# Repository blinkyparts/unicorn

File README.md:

# Rainbow Unicorn

This unicorn will bright up your life. The hair is glowing in all colours of the rainbow due to RGB-LEDs on the back. The soldering kit is very simple and easy to assamble.

The RGB-Effect looks like this, but much better in real :)

- Status: **Complete**
- Difficulty: **2/5**

### Parts List

| Description                   | Quantity |
|-------------------------------|----------|
| RGB LEDs 5mm                  |     4    |
| Button (SMD)                  |     1    |
| CR2032 Battery Holder (SMD)   |     1    |
| CR2032 Battery (not included) |     1    |

### Manual
You can find the manual and pictures of every step here: https://github.com/Binary-Kitchen/SolderingTutorial

### Copyright and Authorship

- Board: [CC-BY-SA 4.0](https://creativecommons.org/licenses/by-sa/4.0/) - Binary Kitchen e.V. and blinkyparts.com
- Unicorn SVG [CC-BY-SA](https://creativecommons.org/licenses/by-sa/4.0/) - [Unicorn by Mooms from the Noun Project](https://thenounproject.com/term/unicorn/2061795/) (We've bought a licence, you should honor the artist work too!)
- Idea and scheme: [CC-BY-SA 4.0](https://creativecommons.org/licenses/by-sa/4.0/) - [Timo Schindler @ blinkyparts.com](https://blinkyparts.com)

### Buy Soldering Kits
If you want to buy the parts and PCB for a soldering kit you can find everything here: [shop.blinkyparts.com](https://shop.blinkyparts.com/de/Regenbogen-Einhorn-Einfacher-Bausatz-fuer-einen-tollen-Anstecker/blink232242)

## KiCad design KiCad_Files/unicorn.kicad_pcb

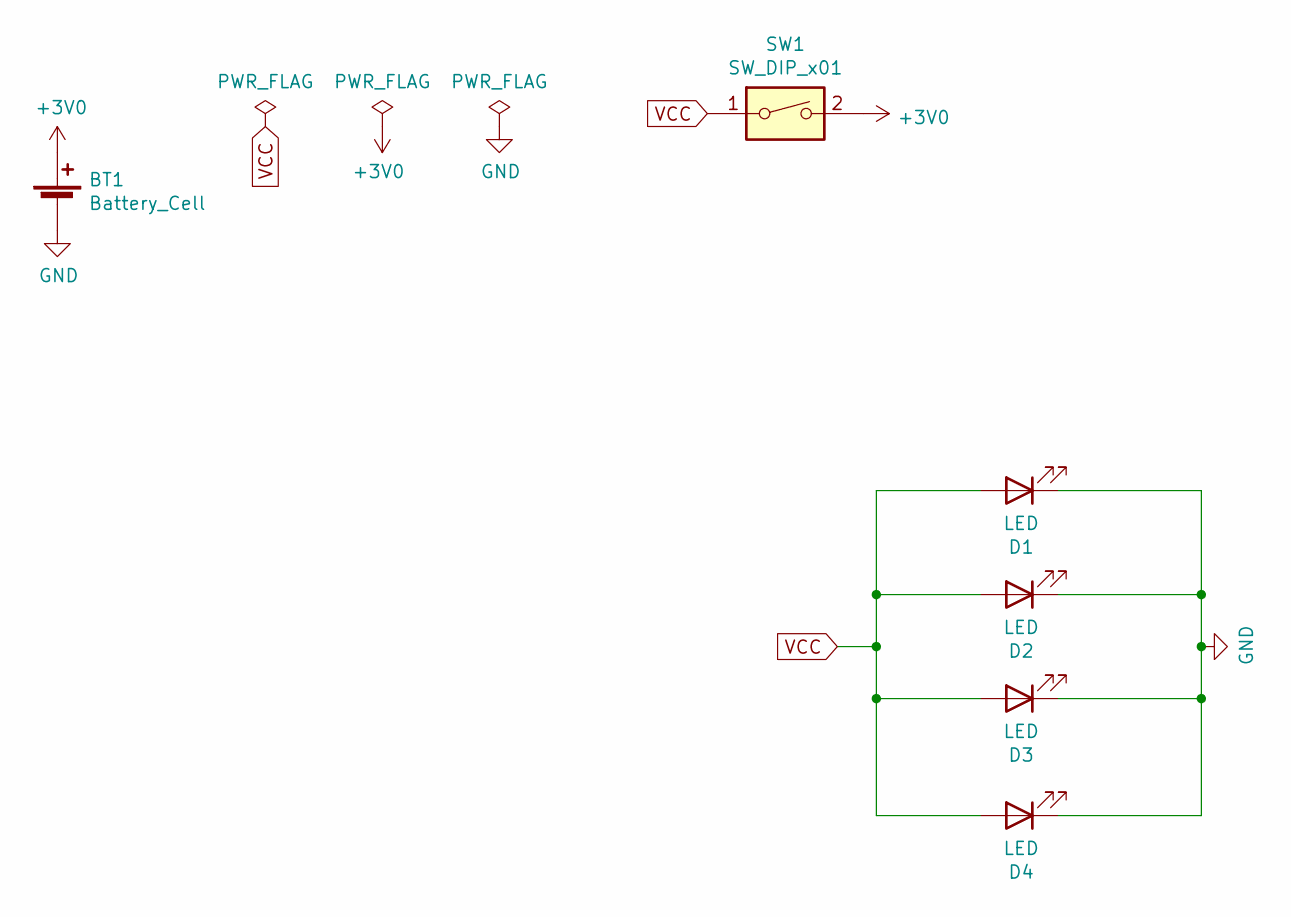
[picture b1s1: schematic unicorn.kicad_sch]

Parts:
BT1: Battery_Cell; BatteryHolder_Keystone_1060_1x2032
D1, D2, D3, D4: LED; 5mm_SMD-Pad
SW1: SW_DIP_x01; Push_Button

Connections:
+3V0: BT1.1 (+), SW1.2
GND: BT1.2 (-), D1.1 (K), D2.1 (K), D3.1 (K), D4.1 (K)
VCC: D1.2 (A), D2.2 (A), D3.2 (A), D4.2 (A), SW1.1

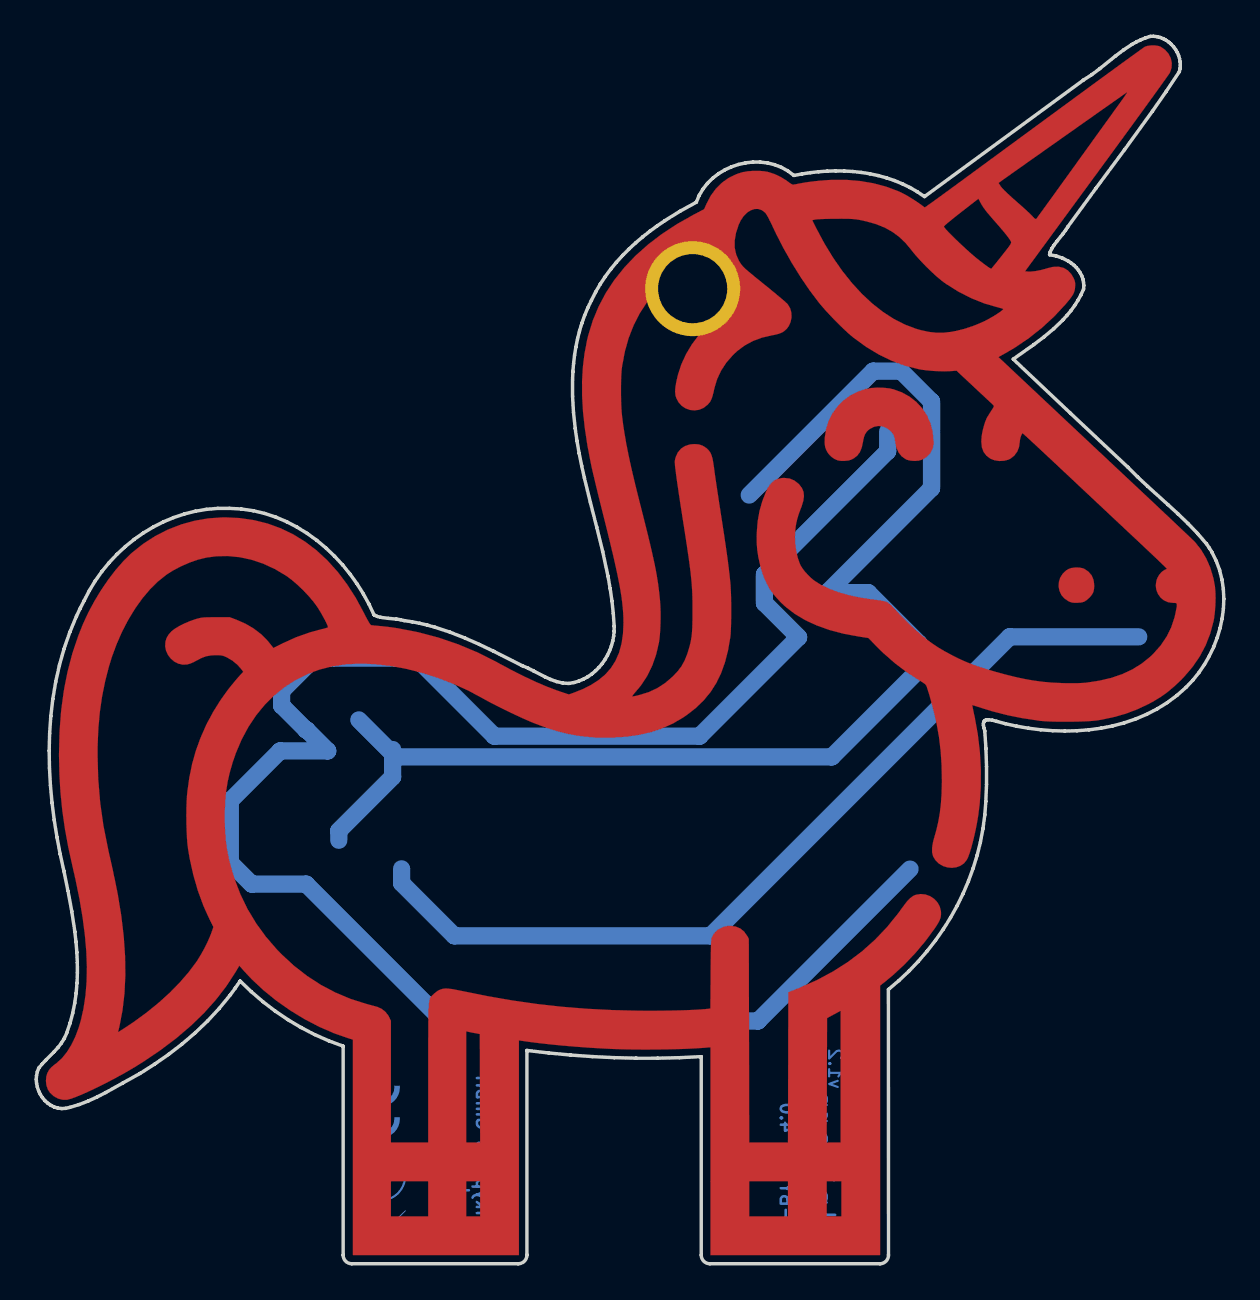
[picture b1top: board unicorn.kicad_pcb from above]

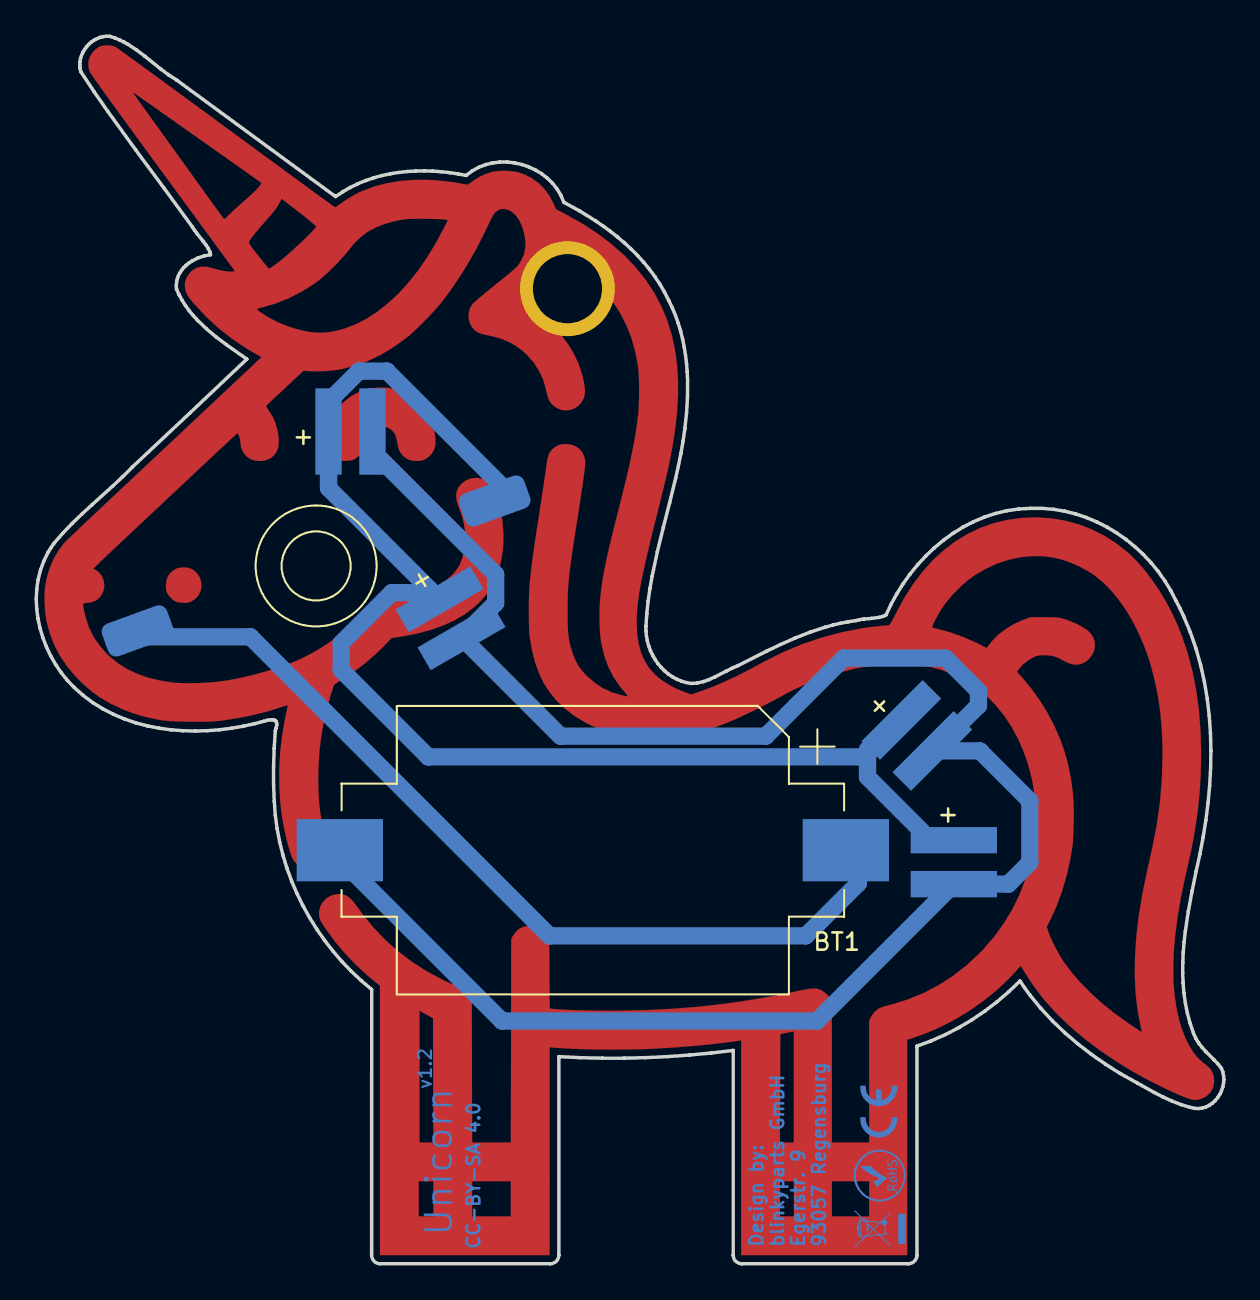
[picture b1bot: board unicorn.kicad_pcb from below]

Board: 2 copper layers, 68.8 x 71.1 mm, 10 parts (9 on the bottom side), 3 nets.

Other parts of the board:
Ref**: Val**; unicorn01
ce_icon_mask_cu_3mm: G***; ce-icon_Mask_Cu_3mm
rohs_icon_mask_cu_3mm: G***; rohs-icon_Mask_Cu_3mm
weee_icon_mask_cu_3mm: G***; weee-icon_Mask_Cu_3mm

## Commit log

2021-01-17 inital commit
2021-01-31 updated the gerber files
2021-01-31 added bought SVG
2021-01-31 added license files
2021-01-31 added readme
2023-04-19 deleted not needed footprints
2023-04-19 added new battery holder
2023-04-19 added kicad specific gitignore
2023-04-19 added new footprint for push button
2023-04-19 removed old files
2023-04-19 added new gerber files
2023-04-19 modified pcb to version 1.1
2023-04-19 added old 1.0 version for legacy mode
2023-04-19 new scheme and project format
2023-04-19 added new bom-file
2023-04-19 modified readme
2025-03-11 added case from binary kitchen repo
2025-09-24 added new files for 1.2
